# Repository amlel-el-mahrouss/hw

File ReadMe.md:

# MHR-0002

The MHR-0002 KiCad board.
You need:

- KiCad EDA.

##### Copyright, Amlal El Mahrouss, all rights reserved.

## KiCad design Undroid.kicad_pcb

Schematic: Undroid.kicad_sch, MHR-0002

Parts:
ANT1: Antenna; Johanson_2450AT18x100
BRIDGE_CHIP1: ATSAME70J19A-AN; LQFP-64_10x10mm_P0.5mm
C1: 100n; C_0402_1005Metric
CPU_1A1: Allwinner-A13; QFP40P2200X2200X160-177N; PARTREV V1.4.0
CPU_GND_1: 15OR; R_0201_0603Metric
D1: LED; LED_PLCC-2_3x2mm_AK
DDR_RAM1: AS4C256M16D3; BGA-96_9.0x13.0mm_Layout2x3x16_P0.8mm
FLASH_MEM_MASS1: XTSD08G; LGA-8_8x6mm_P1.27mm
FLASH_MEM_OS1: XTSD08G; LGA-8_8x6mm_P1.27mm
GND_BRIDGE_R1: 15OR; R_0201_0603Metric
GPU_A1: Allwinner-A13; QFP40P2200X2200X160-177N; PARTREV V1.4.0
MBCI_0: AVR32DB32x-xRXB; QFN-32-1EP_5x5mm_P0.5mm_EP3.1x3.1mm
MBCI_AUDIO0: Conn_01x15; PinHeader_1x15_P1.00mm_Vertical
MBCI_IO1: Conn_01x15; PinHeader_1x15_P1.00mm_Vertical
MBCI_NETWORK1: Conn_01x15; PinHeader_1x15_P1.00mm_Vertical
MBCI_PWR1: Conn_01x15; PinHeader_1x15_P1.00mm_Vertical
MBCI_PWR_R1: 15OR; R_0201_0603Metric
MBCI_VIDEO1: Conn_01x15; PinHeader_1x15_P1.00mm_Vertical
MCU_PWR_R1, MCU_PWR_R2: 15OR; R_0201_0603Metric
NETLIGHT_R1: 15OR; R_0201_0603Metric
RAM_GND_VSSQ_R1: 15OR; R_0201_0603Metric
RAM_GND_VSS_R1, RAM_GND_VSS_R3: 15OR; R_0201_0603Metric
RAM_PWR_R2: 15OR; R_0201_0603Metric
RVSS_S_1: 15OR; R_0201_0603Metric
SD_SLOT_1: Micro_SD_Card; microSD_HC_Molex_104031-0811
SIM_CHIP1: SIM7020C; SIMCom_SIM800C
SIM_SLOT_1: JAE_SIM_Card_SF72S006
VBAT_R1: 15OR; R_0201_0603Metric
VCC_FL_1, VCC_FL_2: 15OR; R_0201_0603Metric
VCC_S_1: 15OR; R_0201_0603Metric
VSS_FL_1, VSS_FL_2: 15OR; R_0201_0603Metric
VSS_SD_VDD1: 15OR; R_0201_0603Metric
VSS_SD_VSS1: 15OR; R_0201_0603Metric

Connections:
3.3V: MBCI_IO1.8, MBCI_NETWORK1.8, MBCI_VIDEO1.8
A0: BRIDGE_CHIP1.54 (PD4), CPU_1A1.64 (DDR3_A0), DDR_RAM1.N3 (A0); also elsewhere on the board
A1: BRIDGE_CHIP1.53 (PD5), CPU_1A1.52 (DDR3_A1), DDR_RAM1.P7 (A1); also elsewhere on the board
A2: BRIDGE_CHIP1.51 (PD6), CPU_1A1.66 (DDR3_A2), DDR_RAM1.P3 (A2); also elsewhere on the board
A3: BRIDGE_CHIP1.50 (PD7), CPU_1A1.65 (DDR3_A3), DDR_RAM1.N2 (A3); also elsewhere on the board
A4: BRIDGE_CHIP1.49 (PD8), CPU_1A1.51 (DDR3_A4), DDR_RAM1.P8 (A4); also elsewhere on the board
A5: BRIDGE_CHIP1.48 (PD9), CPU_1A1.67 (DDR3_A5), DDR_RAM1.P2 (A5); also elsewhere on the board
A6: BRIDGE_CHIP1.44 (PD10), CPU_1A1.54 (DDR3_A6), DDR_RAM1.R8 (A6); also elsewhere on the board
A7: BRIDGE_CHIP1.43 (PD11), CPU_1A1.71 (DDR3_A7), DDR_RAM1.R2 (A7); also elsewhere on the board
A8: BRIDGE_CHIP1.41 (PD12), CPU_1A1.55 (DDR3_A8), DDR_RAM1.T8 (A8); also elsewhere on the board
A9: BRIDGE_CHIP1.26 (PD21), CPU_1A1.69 (DDR3_A9), DDR_RAM1.R3 (A9); also elsewhere on the board
A10/AP: BRIDGE_CHIP1.25 (PD22), CPU_1A1.48 (DDR3_A10), DDR_RAM1.L7 (A10/AP); also elsewhere on the board
A11: BRIDGE_CHIP1.22 (PD24), CPU_1A1.56 (DDR3_A11), DDR_RAM1.R7 (A11), MBCI_0.11 (PD1); also elsewhere on the board
A12/BC_N: CPU_1A1.50 (DDR3_A12), DDR_RAM1.N7 (A12/~BC), MBCI_0.12 (PD2); also elsewhere on the board
A13: CPU_1A1.68 (DDR3_A13), DDR_RAM1.T3 (A13), MBCI_0.13 (PD3); also elsewhere on the board
A14: CPU_1A1.57 (DDR3_A14), DDR_RAM1.T7 (A14), MBCI_0.14 (PD4); also elsewhere on the board
ALPHA_V: MBCI_0.9 (PC3), MBCI_VIDEO1.4
AVAIL_N: MBCI_0.30 (XTALHF1/PA0), MBCI_NETWORK1.6
BLUE_V: MBCI_0.22 (PF2), MBCI_VIDEO1.3
BT_CLK3: MBCI_NETWORK1.12
CLK: MBCI_IO1.11, MBCI_NETWORK1.11, MBCI_VIDEO1.11
CMD_F1: BRIDGE_CHIP1.56 (PD2), FLASH_MEM_MASS1.5 (CMD/DI)
CMD_F2: BRIDGE_CHIP1.55 (PD3), FLASH_MEM_OS1.5 (CMD/DI)
CONN_NMI_N: CPU_1A1.158 (NMI_N), MBCI_IO1.4; also elsewhere on the board
CPU_PWR: CPU_1A1.4 (VDD_CPU), CPU_1A1.5 (VCC), CPU_1A1.9 (VDD_CPU), CPU_1A1.11 (VDD_CPU), CPU_1A1.16 (VDD_CPU), CPU_1A1.35 (VDD_INT), CPU_1A1.73 (VDD_INT), CPU_1A1.98 (VDD_INT), CPU_1A1.100 (VCC), CPU_1A1.109 (VDD_INT), CPU_1A1.142 (VCC), CPU_1A1.149 (VDD_INT), CPU_1A1.156 (VDD_CPU), CPU_1A1.163 (VCC), CPU_1A1.164 (VDD_CPU), CPU_1A1.169 (VDD_CPU), CPU_1A1.173 (VDD_CPU), MCU_PWR_R2.1; also elsewhere on the board
CTS1: BRIDGE_CHIP1.11 (PB3), SIM_CHIP1.4 (UART1_CTS)
DAT0_BT2: MBCI_NETWORK1.13
DAT0_N: MBCI_0.3 (PA5), MBCI_NETWORK1.1
DAT1_BT1: MBCI_NETWORK1.14
DAT1_N: MBCI_0.2 (PA4), MBCI_NETWORK1.2
DAT2_N: MBCI_0.1 (PA3), MBCI_NETWORK1.3
DAT3_N: MBCI_0.32 (PA2), MBCI_NETWORK1.4
DAT4_N: MBCI_0.31 (XTALHF2/PA1), MBCI_NETWORK1.5
DCD1: BRIDGE_CHIP1.30 (PA27), SIM_CHIP1.5 (UART1_DCD)
DQ00: CPU_1A1.22 (DDR3_D0), DDR_RAM1.E3 (DQ0); also elsewhere on the board
DQ01: CPU_1A1.40 (DDR3_D1), DDR_RAM1.F7 (DQ1); also elsewhere on the board
DQ02: CPU_1A1.21 (DDR3_D2), DDR_RAM1.F2 (DQ2); also elsewhere on the board
DQ03: CPU_1A1.41 (DDR3_D3), DDR_RAM1.F8 (DQ3); also elsewhere on the board
DQ04: CPU_1A1.19 (DDR3_D4), DDR_RAM1.H3 (DQ4); also elsewhere on the board
DQ05: CPU_1A1.44 (DDR3_D5), DDR_RAM1.H8 (DQ5); also elsewhere on the board
DQ06: CPU_1A1.20 (DDR3_D6), DDR_RAM1.G2 (DQ6); also elsewhere on the board
DQ07: CPU_1A1.42 (DDR3_D7), DDR_RAM1.H7 (DQ7); also elsewhere on the board
DQ08: CPU_1A1.37 (DDR3_D8), DDR_RAM1.D7 (DQ8); also elsewhere on the board
DQ09: CPU_1A1.25 (DDR3_D9), DDR_RAM1.C3 (DQ9); also elsewhere on the board
DQ10: CPU_1A1.39 (DDR3_D10), DDR_RAM1.C8 (DQ10); also elsewhere on the board
DQ11: CPU_1A1.24 (DDR3_D11), DDR_RAM1.C2 (DQ11); also elsewhere on the board
DQ12: CPU_1A1.36 (DDR3_D12), DDR_RAM1.A7 (DQ12); also elsewhere on the board
DQ13: CPU_1A1.26 (DDR3_D13), DDR_RAM1.A2 (DQ13); also elsewhere on the board
DQ14: CPU_1A1.38 (DDR3_D14), DDR_RAM1.B8 (DQ14); also elsewhere on the board
DQ15: CPU_1A1.27 (DDR3_D15), DDR_RAM1.A3 (DQ15); also elsewhere on the board
DRAM_PWR: CPU_1A1.23 (VCC_DRAM), CPU_1A1.30 (VCC_DRAM), CPU_1A1.43 (VCC_DRAM), CPU_1A1.53 (VCC_DRAM), CPU_1A1.62 (VCC_DRAM), RAM_PWR_R2.2; also elsewhere on the board
DTR1: BRIDGE_CHIP1.17 (PA22), SIM_CHIP1.6 (UART1_DTR)
GND: BRIDGE_CHIP1.5 (VREFP), BRIDGE_CHIP1.45 (JTAGSEL), CPU_1A1.84 (MICIN1), CPU_1A1.86 (LRADC), CPU_1A1.87 (TPX2), CPU_1A1.88 (TPY2), CPU_1A1.89 (TPX1), CPU_1A1.90 (TPY1), CPU_GND_1.1, D1.1 (K), GND_BRIDGE_R1.2, MBCI_IO1.15, MBCI_NETWORK1.15, MBCI_VIDEO1.15, RAM_GND_VSS_R1.1, RAM_GND_VSS_R3.1, RVSS_S_1.2, SIM_CHIP1.8 (GND), SIM_CHIP1.12 (RTC_EINT), SIM_CHIP1.13 (GND), SIM_CHIP1.19 (GND), SIM_CHIP1.21 (GND), SIM_CHIP1.24 (USB_VBUS), SIM_CHIP1.27 (GND), SIM_CHIP1.30 (GND), SIM_CHIP1.31 (GND), SIM_CHIP1.33 (GND), SIM_CHIP1.36 (GND), SIM_CHIP1.37 (GND), VSS_FL_1.2, VSS_FL_2.2; also elsewhere on the board
GREEN_V: MBCI_0.21 (XTAL32K2/PF1), MBCI_VIDEO1.2
GSM_GPIO_0: BRIDGE_CHIP1.32 (PA5), SIM_CHIP1.10 (GPIO0)
GSM_GPIO_1: BRIDGE_CHIP1.15 (PA7), SIM_CHIP1.29 (GPIO1)
GSM_IO: BRIDGE_CHIP1.40 (PA3), SIM_CHIP1.15 (SIM_DATA), SIM_SLOT_1.C7 (I/O)
GSM_PWR_N: MBCI_IO1.6, SIM_CHIP1.39 (~PWRKEY)
GSM_RST: SIM_CHIP1.17 (SIM_RST), SIM_SLOT_1.C2 (RST)
GSM_RST_N: MBCI_IO1.7, SIM_CHIP1.28 (~RESET)
GSM_STATUS: BRIDGE_CHIP1.38 (PB12), SIM_CHIP1.42 (STATUS)
GSM_VPP: BRIDGE_CHIP1.34 (PA4), SIM_CHIP1.14 (SIM_DET), SIM_SLOT_1.C6 (VPP/SWP)
HSYNC_V: MBCI_0.8 (PC2), MBCI_VIDEO1.5
LDM_RAM: DDR_RAM1.E7 (LDM)
MCU_PWR: BRIDGE_CHIP1.4 (VDDIN), BRIDGE_CHIP1.10 (VDDIO), BRIDGE_CHIP1.13 (VDDCORE), BRIDGE_CHIP1.24 (VDDCORE), BRIDGE_CHIP1.42 (VDDIO), BRIDGE_CHIP1.52 (VDDPLL), BRIDGE_CHIP1.58 (VDDIO), BRIDGE_CHIP1.61 (VDDCORE), BRIDGE_CHIP1.64 (VDDPLLUSB), MCU_PWR_R1.1
MCU_UBOOT_RX: BRIDGE_CHIP1.33 (PA9), MBCI_IO1.13
MCU_UBOOT_TX: BRIDGE_CHIP1.28 (PA10), MBCI_IO1.14
unnamed: ANT1.1 (A), SIM_CHIP1.32 (ANT)
unnamed: BRIDGE_CHIP1.6 (GND), BRIDGE_CHIP1.14 (GND), BRIDGE_CHIP1.31 (GND), GND_BRIDGE_R1.1
unnamed: C1.2, MBCI_0.29 (GND), MBCI_0.33 (GND), RAM_GND_VSS_R3.2
unnamed: CPU_1A1.177 (GND), CPU_GND_1.2
unnamed: D1.2 (A), NETLIGHT_R1.1
unnamed: DDR_RAM1.B2 (VDD), DDR_RAM1.D9 (VDD), DDR_RAM1.G7 (VDD), DDR_RAM1.K2 (VDD), DDR_RAM1.K8 (VDD), DDR_RAM1.N1 (VDD), DDR_RAM1.N9 (VDD), DDR_RAM1.R1 (VDD), DDR_RAM1.R9 (VDD), RAM_PWR_R2.1
unnamed: DDR_RAM1.A9 (VSS), DDR_RAM1.B3 (VSS), DDR_RAM1.E1 (VSS), DDR_RAM1.G8 (VSS), DDR_RAM1.J2 (VSS), DDR_RAM1.J8 (VSS), DDR_RAM1.M1 (VSS), DDR_RAM1.M9 (VSS), DDR_RAM1.P1 (VSS), DDR_RAM1.P9 (VSS), DDR_RAM1.T1 (VSS), DDR_RAM1.T9 (VSS), RAM_GND_VSS_R1.2
unnamed: DDR_RAM1.B1 (VSSQ), DDR_RAM1.B9 (VSSQ), DDR_RAM1.D1 (VSSQ), DDR_RAM1.D8 (VSSQ), DDR_RAM1.E2 (VSSQ), DDR_RAM1.E8 (VSSQ), DDR_RAM1.F9 (VSSQ), DDR_RAM1.G1 (VSSQ), DDR_RAM1.G9 (VSSQ), RAM_GND_VSSQ_R1.1
unnamed: FLASH_MEM_MASS1.8 (VDD), VCC_FL_1.2
unnamed: FLASH_MEM_MASS1.4 (VSS), VSS_FL_1.1
unnamed: FLASH_MEM_OS1.8 (VDD), VCC_FL_2.2
unnamed: FLASH_MEM_OS1.4 (VSS), VSS_FL_2.1
unnamed: C1.1, MBCI_0.28 (VDD), MBCI_PWR_R1.1
unnamed: SD_SLOT_1.4 (VDD), VSS_SD_VDD1.1
unnamed: SD_SLOT_1.6 (VSS), VSS_SD_VSS1.1
unnamed: NETLIGHT_R1.2, SIM_CHIP1.41 (NETLIGHT)
unnamed: SIM_CHIP1.34 (VBAT), SIM_CHIP1.35 (VBAT), VBAT_R1.2
unnamed: RVSS_S_1.1, SIM_SLOT_1.C5 (GND)
unnamed: SIM_SLOT_1.C1 (VCC), VCC_S_1.1
RAM_BA0: BRIDGE_CHIP1.20 (PD25), CPU_1A1.63 (DDR3_BA0), DDR_RAM1.M2 (BA0), MBCI_0.17 (VREFA/PD7); also elsewhere on the board
RAM_BA1: BRIDGE_CHIP1.21 (PD26), CPU_1A1.49 (DDR3_BA1), DDR_RAM1.N8 (BA1), MBCI_0.16 (PD6); also elsewhere on the board
RAM_BA2: BRIDGE_CHIP1.2 (PD31), CPU_1A1.61 (DDR3_BA2), DDR_RAM1.M3 (BA2), MBCI_0.15 (PD5); also elsewhere on the board
RAM_CAS_N: CPU_1A1.58 (DDR3_RAS), DDR_RAM1.K3 (~CAS); also elsewhere on the board
RAM_CK: CPU_1A1.45 (DDR3_CK), DDR_RAM1.J7 (CK); also elsewhere on the board
RAM_CKE: CPU_1A1.47 (DDR3_CKE), DDR_RAM1.K9 (CKE); also elsewhere on the board
RAM_CK_N: CPU_1A1.46 (DDR3_CK_N), DDR_RAM1.K7 (~CK); also elsewhere on the board
RAM_CS_N: DDR_RAM1.L2 (~CS)
RAM_LDQS: CPU_1A1.33 (DDR3_DQS1), DDR_RAM1.F3 (LDQS); also elsewhere on the board
RAM_LDQS_N: CPU_1A1.34 (DDR3_DQS1_N), DDR_RAM1.G3 (~LDQS); also elsewhere on the board
RAM_ODT: CPU_1A1.72 (DDR3_ODT), DDR_RAM1.K1 (ODT); also elsewhere on the board
RAM_RAS_N: CPU_1A1.59 (DDR3_CAS), DDR_RAM1.J3 (~RAS); also elsewhere on the board
RAM_RST: CPU_1A1.70 (DDR3_RST), DDR_RAM1.T2 (~RESET); also elsewhere on the board
RAM_UDQS: CPU_1A1.31 (DDR3_DQS0), DDR_RAM1.C7 (UDQS); also elsewhere on the board
RAM_UDQS_N: CPU_1A1.32 (DDR3_DQS0_N), DDR_RAM1.B7 (~UDQS); also elsewhere on the board
RAM_WE_N: CPU_1A1.60 (DDR3_WE), DDR_RAM1.L3 (~WE); also elsewhere on the board
RED_V: MBCI_0.20 (XTAL32K1/PF0), MBCI_VIDEO1.1
RESET_N: BRIDGE_CHIP1.36 (NRST), CPU_1A1.159 (RESET_N), MBCI_0.26 (~RESET/PF6), MBCI_IO1.2; also elsewhere on the board
RI1: BRIDGE_CHIP1.23 (PA24), SIM_CHIP1.7 (UART1_RI)
RTC_IN: CPU_1A1.92 (X24MIN), MBCI_IO1.3, SIM_CHIP1.16 (SIM_CLK); also elsewhere on the board
RTC_OUT: CPU_1A1.91 (X24MOUT), FLASH_MEM_MASS1.3 (CLK), FLASH_MEM_OS1.3 (CLK), SD_SLOT_1.5 (CLK), SIM_SLOT_1.C3 (CLK); also elsewhere on the board
RTS1: BRIDGE_CHIP1.8 (PB0), SIM_CHIP1.3 (UART1_RTS)
RX1: BRIDGE_CHIP1.9 (PB2), SIM_CHIP1.2 (UART1_RXD)
RX2: MBCI_0.24 (PF4), SIM_CHIP1.23 (UART2_RXD)
SD0_F1: BRIDGE_CHIP1.16 (PA8), FLASH_MEM_MASS1.6 (SD0/DO)
SD0_F2: BRIDGE_CHIP1.19 (PA14), FLASH_MEM_OS1.6 (SD0/DO)
SD1_F1: BRIDGE_CHIP1.27 (PA11), FLASH_MEM_MASS1.7 (SD1)
SD1_F2: BRIDGE_CHIP1.12 (PA21), FLASH_MEM_OS1.7 (SD1)
SD2_F1: BRIDGE_CHIP1.46 (PB4), FLASH_MEM_MASS1.1 (SD2)
SD2_F2: BRIDGE_CHIP1.29 (PA12), FLASH_MEM_OS1.1 (SD2)
SD3_F1: BRIDGE_CHIP1.47 (PB5), FLASH_MEM_MASS1.2 (SD3/~CS)
SD3_F2: BRIDGE_CHIP1.18 (PA13), FLASH_MEM_OS1.2 (SD3/~CS)
SD_CD_OR_DAT3: BRIDGE_CHIP1.39 (PB7), SD_SLOT_1.2 (DAT3/CD)
SD_CMD: BRIDGE_CHIP1.1 (PD0), BRIDGE_CHIP1.57 (PD1), SD_SLOT_1.3 (CMD)
SD_DAT0: BRIDGE_CHIP1.62 (PB8), SD_SLOT_1.7 (DAT0)
SD_DAT1: BRIDGE_CHIP1.63 (PB9), SD_SLOT_1.8 (DAT1)
SD_DAT2: BRIDGE_CHIP1.35 (PB6), SD_SLOT_1.1 (DAT2)
SND_CLK: MBCI_AUDIO0.15
SND_IN: MBCI_AUDIO0.1, SIM_CHIP1.38 (ADC)
SND_OUT: MBCI_AUDIO0.2
TX1: BRIDGE_CHIP1.7 (PB1), SIM_CHIP1.1 (UART1_TXD)
TX2: MBCI_0.23 (PF3), SIM_CHIP1.22 (UART2_TXD)
UBOOT: CPU_1A1.157 (UBOOT), MBCI_IO1.9; also elsewhere on the board
UBOOT_MBCI: MBCI_0.27 (UPDI), MBCI_IO1.1, MBCI_IO1.5
UDM_RAM: DDR_RAM1.D3 (UDM)
VBUS_USBC: MBCI_PWR1.1, MBCI_PWR_R1.2, MCU_PWR_R1.2, MCU_PWR_R2.2, VBAT_R1.1, VCC_FL_1.1, VCC_FL_2.1, VCC_S_1.2, VSS_SD_VDD1.2, VSS_SD_VSS1.2
VSSQ: RAM_GND_VSSQ_R1.2
VSYNC_V: MBCI_0.7 (PC1), MBCI_VIDEO1.6
ZQ: CPU_1A1.17 (DZQ), DDR_RAM1.L8 (ZQ); also elsewhere on the board

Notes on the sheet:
MBCI Audio
Bridge Power CPU Power MBCI based
MBCI_CTRL
Bridge MCU
Memory (SIM, Flash, SD)
SUNXI A13 CPU
SUNXI A13 GPU
MBCI controller is DMA only
MBCI IO
MBCI NET
DDR3 RAM
LTE module
And reset circuit
MBCI VIDEO

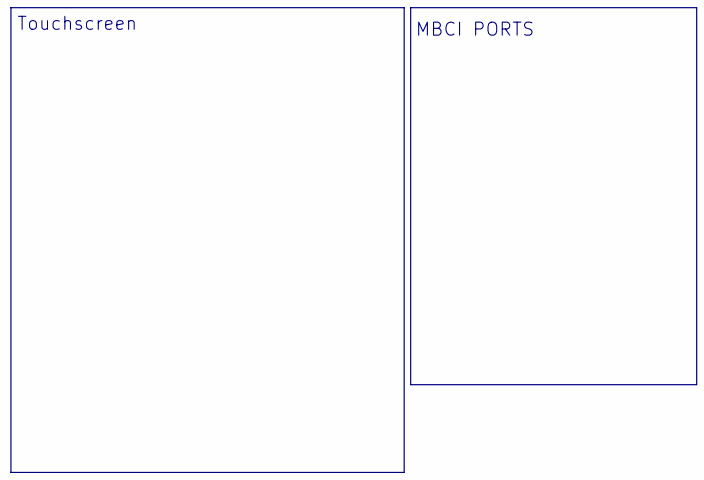
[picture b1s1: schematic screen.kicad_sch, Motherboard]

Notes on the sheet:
Touchscreen
MBCI PORTS

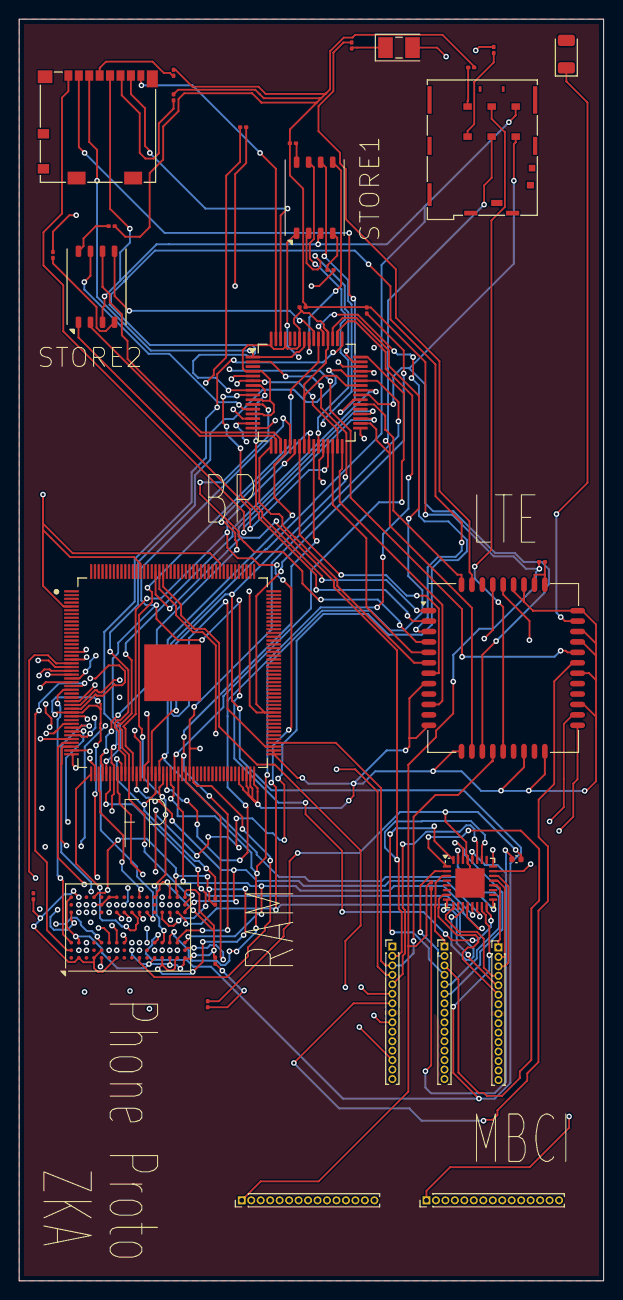
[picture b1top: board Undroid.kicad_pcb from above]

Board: 6 copper layers, 61.7 x 133.2 mm, 35 parts (0 on the bottom side), 125 nets.

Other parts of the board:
CPU_1: Allwinner-A13; QFP40P2200X2200X160-177N

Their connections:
A0: CPU_1.64 (DDR3_A0); also elsewhere on the board
A1: CPU_1.52 (DDR3_A1); also elsewhere on the board
A2: CPU_1.66 (DDR3_A2); also elsewhere on the board
A3: CPU_1.65 (DDR3_A3); also elsewhere on the board
A4: CPU_1.51 (DDR3_A4); also elsewhere on the board
A5: CPU_1.67 (DDR3_A5); also elsewhere on the board
A6: CPU_1.54 (DDR3_A6); also elsewhere on the board
A7: CPU_1.71 (DDR3_A7); also elsewhere on the board
A8: CPU_1.55 (DDR3_A8); also elsewhere on the board
A9: CPU_1.69 (DDR3_A9); also elsewhere on the board
A10/AP: CPU_1.48 (DDR3_A10); also elsewhere on the board
A11: CPU_1.56 (DDR3_A11); also elsewhere on the board
A12/BC_N: CPU_1.50 (DDR3_A12); also elsewhere on the board
A13: CPU_1.68 (DDR3_A13); also elsewhere on the board
A14: CPU_1.57 (DDR3_A14); also elsewhere on the board
CONN_NMI_N: CPU_1.158 (NMI_N); also elsewhere on the board
CPU_PWR: CPU_1.5 (VCC), CPU_1.100 (VCC), CPU_1.142 (VCC), CPU_1.163 (VCC); also elsewhere on the board
DQ00: CPU_1.22 (DDR3_D0); also elsewhere on the board
DQ01: CPU_1.40 (DDR3_D1); also elsewhere on the board
DQ02: CPU_1.21 (DDR3_D2); also elsewhere on the board
DQ03: CPU_1.41 (DDR3_D3); also elsewhere on the board
DQ04: CPU_1.19 (DDR3_D4); also elsewhere on the board
DQ05: CPU_1.44 (DDR3_D5); also elsewhere on the board
DQ06: CPU_1.20 (DDR3_D6); also elsewhere on the board
DQ07: CPU_1.42 (DDR3_D7); also elsewhere on the board
DQ08: CPU_1.37 (DDR3_D8); also elsewhere on the board
DQ09: CPU_1.25 (DDR3_D9); also elsewhere on the board
DQ10: CPU_1.39 (DDR3_D10); also elsewhere on the board
DQ11: CPU_1.24 (DDR3_D11); also elsewhere on the board
DQ12: CPU_1.36 (DDR3_D12); also elsewhere on the board
DQ13: CPU_1.26 (DDR3_D13); also elsewhere on the board
DQ14: CPU_1.38 (DDR3_D14); also elsewhere on the board
DQ15: CPU_1.27 (DDR3_D15); also elsewhere on the board
DRAM_PWR: CPU_1.23 (VCC_DRAM), CPU_1.30 (VCC_DRAM), CPU_1.43 (VCC_DRAM), CPU_1.53 (VCC_DRAM), CPU_1.62 (VCC_DRAM); also elsewhere on the board
GND: CPU_1.84 (MICIN1), CPU_1.86 (LRADC), CPU_1.87 (TPX2), CPU_1.88 (TPY2), CPU_1.89 (TPX1), CPU_1.90 (TPY1); also elsewhere on the board
RAM_BA0: CPU_1.63 (DDR3_BA0); also elsewhere on the board
RAM_BA1: CPU_1.49 (DDR3_BA1); also elsewhere on the board
RAM_BA2: CPU_1.61 (DDR3_BA2); also elsewhere on the board
RAM_CAS_N: CPU_1.58 (DDR3_RAS); also elsewhere on the board
RAM_CK: CPU_1.45 (DDR3_CK); also elsewhere on the board
RAM_CKE: CPU_1.47 (DDR3_CKE); also elsewhere on the board
RAM_CK_N: CPU_1.46 (DDR3_CK_N); also elsewhere on the board
RAM_LDQS: CPU_1.33 (DDR3_DQS1); also elsewhere on the board
RAM_LDQS_N: CPU_1.34 (DDR3_DQS1_N); also elsewhere on the board
RAM_ODT: CPU_1.72 (DDR3_ODT); also elsewhere on the board
RAM_RAS_N: CPU_1.59 (DDR3_CAS); also elsewhere on the board
RAM_RST: CPU_1.70 (DDR3_RST); also elsewhere on the board
RAM_UDQS: CPU_1.31 (DDR3_DQS0); also elsewhere on the board
RAM_UDQS_N: CPU_1.32 (DDR3_DQS0_N); also elsewhere on the board
RAM_WE_N: CPU_1.60 (DDR3_WE); also elsewhere on the board
RESET_N: CPU_1.159 (RESET_N); also elsewhere on the board
RTC_IN: CPU_1.92 (X24MIN); also elsewhere on the board
RTC_OUT: CPU_1.91 (X24MOUT); also elsewhere on the board
UBOOT: CPU_1.157 (UBOOT); also elsewhere on the board
ZQ: CPU_1.17 (DZQ); also elsewhere on the board

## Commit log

2024-06-09 master: initial commit.
2024-06-10 main: Update schematic.
2024-06-10 main: update schematic. Use MIPS MCU.
2024-06-10 Schematic: Update MCU.
2024-06-11 Almost there with POC.
2024-06-11 main: Add PDF, improve PCB and fix schematic.
2024-06-12 main: fix USB-C plug orientation.
2024-06-13 update PCB, increase size.
2024-06-14 main: do not show symbol data sheet for sd-card.
2024-06-14 main: Update PDF technical information.
2024-06-14 Update PDF.
2024-06-15 main: update PDF.
2024-06-15 main: New NorthBridge zone, include AllWinner A13 as ARM CPU.
2024-06-15 main: update and fix schematic.
2024-06-15 main: remove useless 10K ohm resistor for CLK.
2024-06-16 main: Update netlist.
2024-06-16 main: Generate new pcb. Need to verify it.
2024-06-16 main: new PCB.
2024-06-17 main: Reworking board now, because of Allwinner QFP package.
2024-06-17 ZET-0001: Working on it, need to route now, and test it.
2024-06-17 main: Doing DRC and ERC right now...
2024-06-17 Adding Resistive touch screen and making it sure that it will pass ERC.
2024-06-17 fix: Include part of Allwinner SoC. fix: Fix ERC and DRC.
2024-06-18 pcb: Fix PCB layout.
2024-06-18 schematic: Fix layout of GPRS resistors in schematics.
2024-06-18 pcb-master: Update prototype.
2024-06-18 pcb-master: Fix schematic and PCB.
2024-06-19 pcb-master: Update PCB.
2024-06-19 pcb-master: update schematic.
2024-06-19 pcb-master: improve schematics to be much more organized.
2024-06-19 pcb-master: improve schematic and PCB.
2024-06-19 update sch.
2024-06-19 pcb-master: update PCB layout.
2024-06-20 Undroid: Fix schematic.
2024-06-22 board: major improvements.
2024-06-22 Finishing routing.
2024-06-23 pcb-master: Start of step 2: Finish and improve routing of motherboard.
2024-06-23 Improving routes.
2024-06-23 Add gerber files, although the PCB isn't finished yet.
2024-06-23 pcb-master: Undroid fixing PCB.
2024-06-23 PCB: Improved it.
2024-06-24 FIX: Rework some layout of DDR3 RAM, which the autorouter did wrong.
2024-06-24 PCB: Finish routing.
2024-06-24 pcb: Add Power plane to third layer.
2024-06-24 PCB: Fix last errors.
2024-06-24 PCB: Fixing routes.
2024-06-25 Generated Gerber files.
2024-06-25 Project: Add spice.
2024-06-25 FIX: Schematic and PCB, Improved those and regenerated zones as well.
2024-06-26 FIX: provide ohm values of resistors in schematic, as well as resistor for CC1.
2024-06-27 IMP: New RESET_N pin
2024-06-27 FIX: 90 deg route in Bridge routes.
2024-06-27 FIX: weird schematic wire. inside RAM
2024-06-27 IMP: bump.
2024-06-27 META: Add screenshot.
2024-06-28 META: Bump.
2024-06-28 GEN: New gerber files.
2024-06-28 pcb-master: Fix PCB (MHR-0002)
2024-06-28 meta: Add Readme.
2024-06-29 Generate gerbers file, fix circuits.
2024-06-29 PCB: Improve planes.
2024-06-29 Undroid: Fix PCB.
2024-06-29 MHR-0002: Final revision of PCB before getting sent out.
2024-06-30 PCB improvements and generated BoM, Gerbers and reports.
2024-06-30 Generated necessary files for production.
2024-06-30 Prototype ready.
2024-06-30 Replace Zeta.pdf with MHR-0002.pdf.
2024-06-30 Board: Finished it.
2024-06-30 Generated gerbers and poses.
2024-06-30 REV 2: PCB revision.
2024-06-30 REV 3: PCB revision. Fix unconnected wires.
2024-06-30 PCBnew: Fix 90 degree track.
2024-06-30 PCB: Fix 90 degree track in B.Cu
2024-06-30 Add MBCI.pdf
2024-07-01 FIX: eeschema: PWR_Flag was too close of edge.
2024-07-01 IMP: Use a 2.4Ghz antenna for the LTE chip.
2024-07-01 IMP: RTC_IN needs to be shorter, made it so.
2024-07-02 Fix tracks regarding the SD_SLOT_1
2024-07-03 pcb: Update prototype schematic, use MBCI ports instead of USB.
2024-07-07 Update ReadMe, add MBCI ports to PCB for audio and power.
2024-07-08 hw: imp: MBCI I/O, but not for BT.
2024-07-12 [IMP] MBCI phone prototype.
2024-07-14 [IMP] Phone prototype done.
    The PCB is disguting a real product will be done after.
2024-07-17 [IMPROVE] PCB routing, getting a way to make a better ram circuit.
2024-07-17 [WIP] Need better connectors for MBCI.
2024-07-17 [FIX] 90s degrees angles and such.
2024-09-13 Ordering PCB now for prototype, saving commit.
2024-11-27 IMP: Update Undroid schematic.
2024-12-27 Improve Undroid's schematics.
